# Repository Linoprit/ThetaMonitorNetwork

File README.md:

# ThetaMonitorNetwork

This project replaces TemperatureMonitor

What it does: Several slaves measure temperature, with DS18B20 and send their results to a master-station, via NRF24 modules. The master-station is connected to a Raspi, which hosts a database and a PHP-Server (LAMP-Config). With a browser, you can graphically see the temperature-profile of the last 24h. In the database every measurement is stored in 5 minute intervals. Also the slaves can drive a relay, to which a heating can be connected.

The old TemperatureMonitor run fine since some years now. Due to some instabilities with DS18B20 measurement, desired sensor extension, etc. I will develop this thing further in this project.

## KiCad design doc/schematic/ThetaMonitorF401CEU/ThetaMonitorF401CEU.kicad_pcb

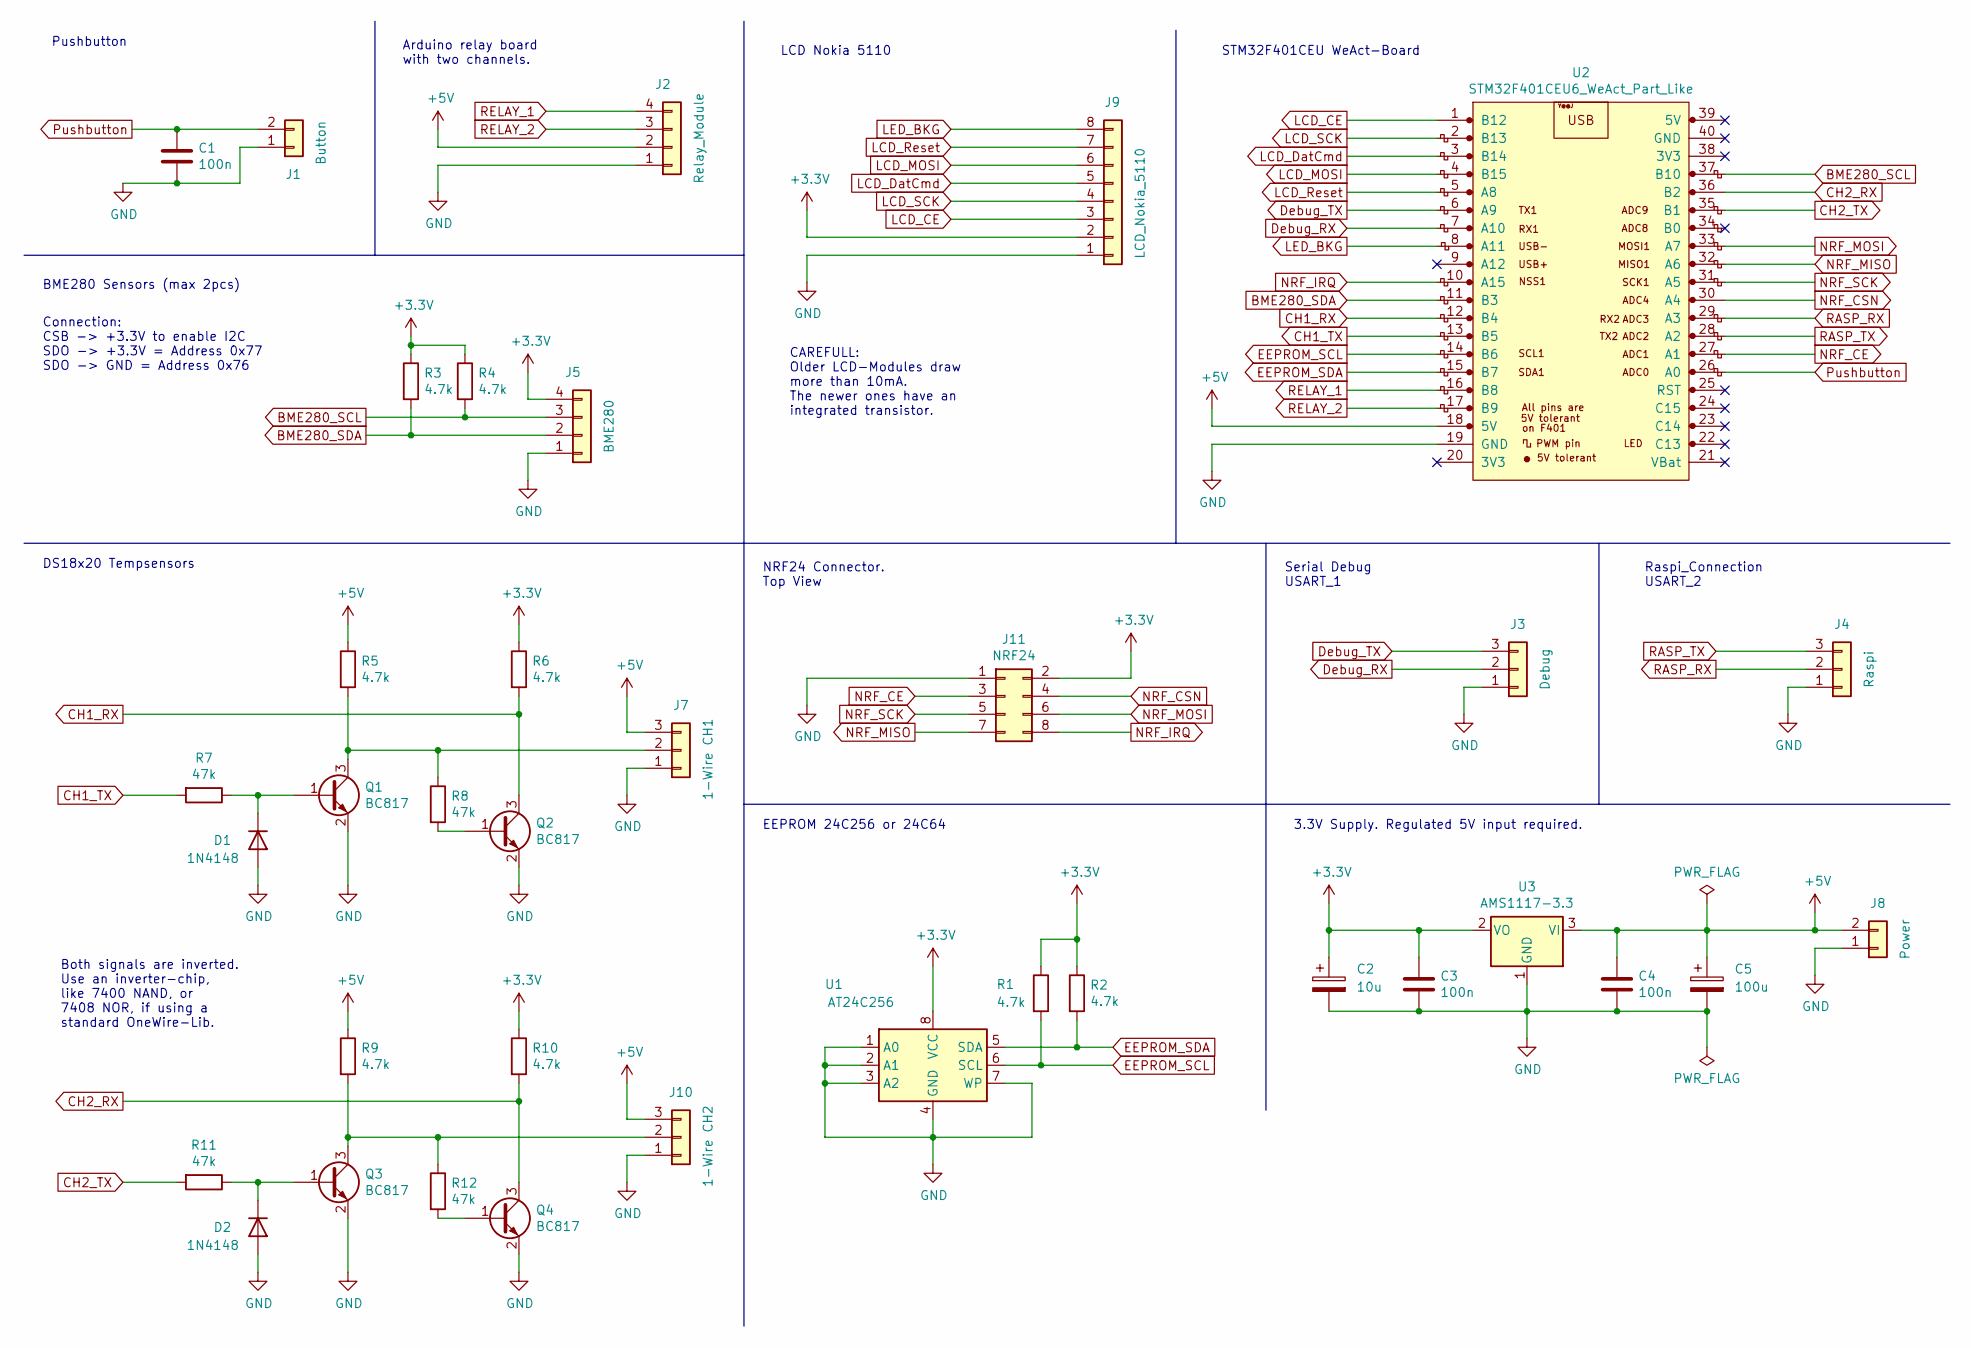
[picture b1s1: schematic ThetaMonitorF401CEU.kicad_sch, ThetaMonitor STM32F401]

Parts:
C1, C3, C4: 100n; C_1206_3216Metric_Pad1.33x1.80mm_HandSolder
C2: 10u; CP_Radial_D6.3mm_P2.50mm
C5: 100u; CP_Axial_L11.0mm_D8.0mm_P15.00mm_Horizontal
D1, D2: 1N4148; D_DO-35_SOD27_P7.62mm_Horizontal
J1: Button; Molex_KK-254_AE-6410-02A_1x02_P2.54mm_Vertical
J2: Relay_Module; Molex_KK-254_AE-6410-04A_1x04_P2.54mm_Vertical
J3: Debug; Molex_KK-254_AE-6410-03A_1x03_P2.54mm_Vertical
J4: Raspi; Molex_KK-254_AE-6410-03A_1x03_P2.54mm_Vertical
J5: BME280; Molex_KK-254_AE-6410-04A_1x04_P2.54mm_Vertical
J7: 1-Wire CH1; Molex_KK-254_AE-6410-03A_1x03_P2.54mm_Vertical
J8: Power; Molex_KK-254_AE-6410-02A_1x02_P2.54mm_Vertical
J9: LCD_Nokia_5110; Molex_KK-254_AE-6410-08A_1x08_P2.54mm_Vertical
J10: 1-Wire CH2; Molex_KK-254_AE-6410-03A_1x03_P2.54mm_Vertical
J11: NRF24; PinHeader_2x04_P2.54mm_Vertical
Q1, Q2, Q3, Q4: BC817; SOT-23
R1, R2, R3, R4, R5, R6, R9, R10: 4.7k; R_Axial_DIN0207_L6.3mm_D2.5mm_P7.62mm_Horizontal
R7, R8, R11, R12: 47k; R_Axial_DIN0207_L6.3mm_D2.5mm_P7.62mm_Horizontal
U1: AT24C256; DIP-8_W7.62mm
U2: STM32F401CEU6_WeAct_Part_Like; YAAJ_BluePill_1
U3: AMS1117-3.3; SOT-223-3_TabPin2

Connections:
+3V3: C2.1, C3.1, J5.4, J9.2, J11.2, R1.1, R2.1, R3.1, R4.1, R6.1, R10.1, U1.8 (VCC), U3.2 (VO)
+5V: C4.1, C5.1, J2.2, J7.3, J8.2, J10.3, R5.1, R9.1, U2.18 (5V), U3.3 (VI)
BME280_SCL: J5.3, R4.2, U2.37 (B10)
BME280_SDA: J5.2, R3.2, U2.11 (B3)
CH1_RX: Q2.3 (C), R6.2, U2.12 (B4)
CH1_TX: R7.2, U2.13 (B5)
CH2_RX: Q4.3 (C), R10.2, U2.36 (B2)
CH2_TX: R11.2, U2.35 (B1)
Debug_RX: J3.2, U2.7 (A10)
Debug_TX: J3.3, U2.6 (A9)
EEPROM_SCL: R1.2, U1.6 (SCL), U2.14 (B6)
EEPROM_SDA: R2.2, U1.5 (SDA), U2.15 (B7)
GND: C1.2, C2.2, C3.2, C4.2, C5.2, D1.2 (A), D2.2 (A), J1.1, J2.1, J3.1, J4.1, J5.1, J7.1, J8.1, J9.1, J10.1, J11.1, Q1.2 (E), Q2.2 (E), Q3.2 (E), Q4.2 (E), U1.1 (A0), U1.2 (A1), U1.3 (A2), U1.4 (GND), U1.7 (WP), U2.19 (GND), U3.1 (GND)
LCD_CE: J9.3, U2.1 (B12)
LCD_DatCmd: J9.5, U2.3 (B14)
LCD_MOSI: J9.6, U2.4 (B15)
LCD_Reset: J9.7, U2.5 (A8)
LCD_SCK: J9.4, U2.2 (B13)
LED_BKG: J9.8, U2.8 (A11)
NRF_CE: J11.3, U2.27 (A1)
NRF_CSN: J11.4, U2.30 (A4)
NRF_IRQ: J11.8, U2.10 (A15)
NRF_MISO: J11.7, U2.32 (A6)
NRF_MOSI: J11.6, U2.33 (A7)
NRF_SCK: J11.5, U2.31 (A5)
unnamed: D1.1 (K), Q1.1 (B), R7.1
unnamed: D2.1 (K), Q3.1 (B), R11.1
unnamed: J7.2, Q1.3 (C), R5.2, R8.1
unnamed: J10.2, Q3.3 (C), R9.2, R12.1
unnamed: Q2.1 (B), R8.2
unnamed: Q4.1 (B), R12.2
Pushbutton: C1.1, J1.2, U2.26 (A0)
RASP_RX: J4.2, U2.29 (A3)
RASP_TX: J4.3, U2.28 (A2)
RELAY_1: J2.4, U2.16 (B8)
RELAY_2: J2.3, U2.17 (B9)

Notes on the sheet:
LCD Nokia 5110
Raspi_Connection USART_2
BME280 Sensors (max 2pcs)
3.3V Supply. Regulated 5V input required.
EEPROM 24C256 or 24C64
Both signals are inverted. Use an inverter-chip, like 7400 NAND, or 7408 NOR, if using a standard OneWire-Lib.
Arduino relay board with two channels.
Pushbutton
STM32F401CEU WeAct-Board
NRF24 Connector. Top View
CAREFULL: Older LCD-Modules draw more than 10mA. The newer ones have an integrated transistor.
DS18x20 Tempsensors
Serial Debug USART_1
Connection: CSB -> +3.3V to enable I2C SDO -> +3.3V = Address 0x77 SDO -> GND = Address 0x76

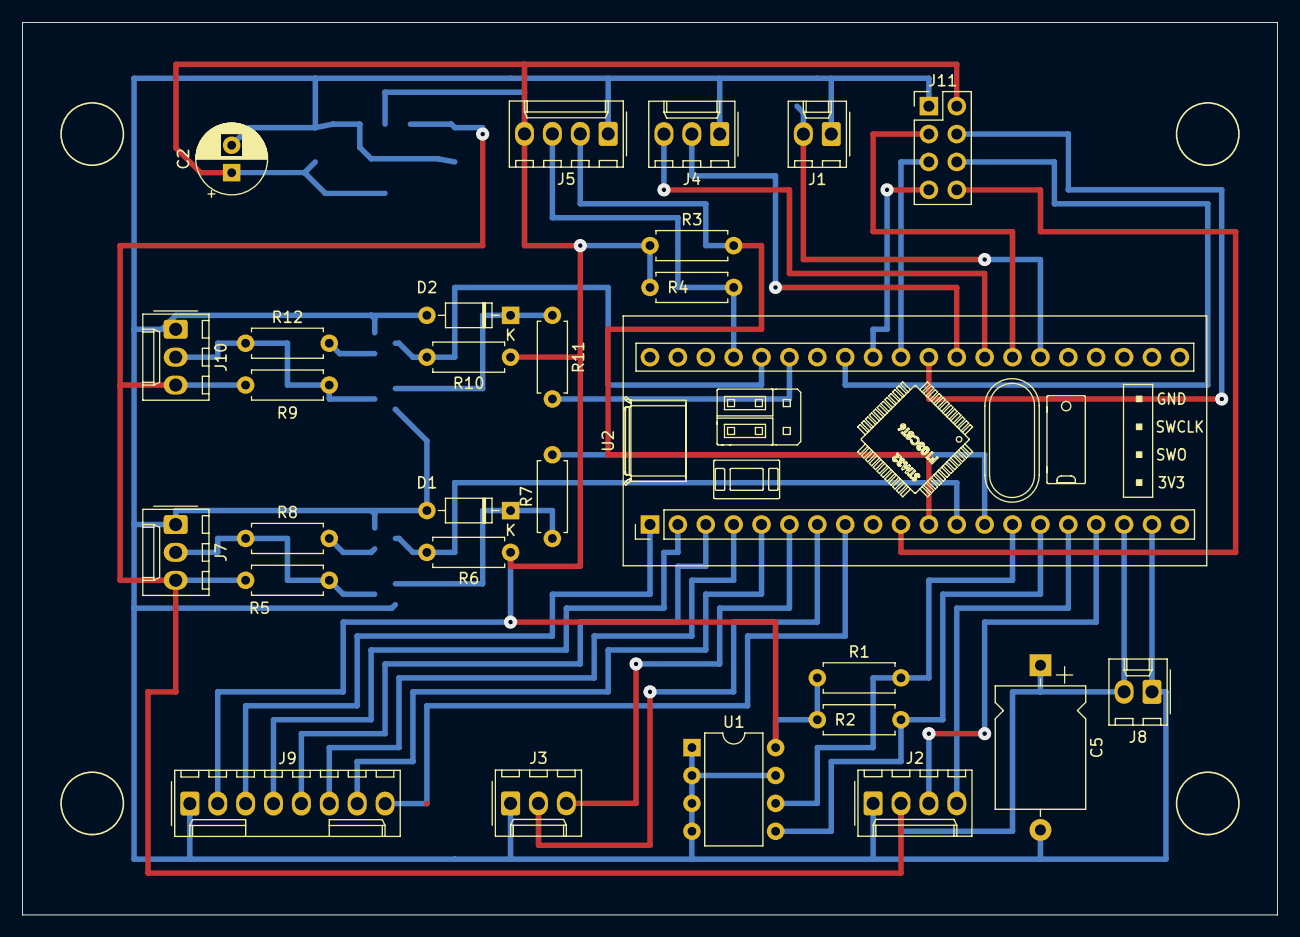
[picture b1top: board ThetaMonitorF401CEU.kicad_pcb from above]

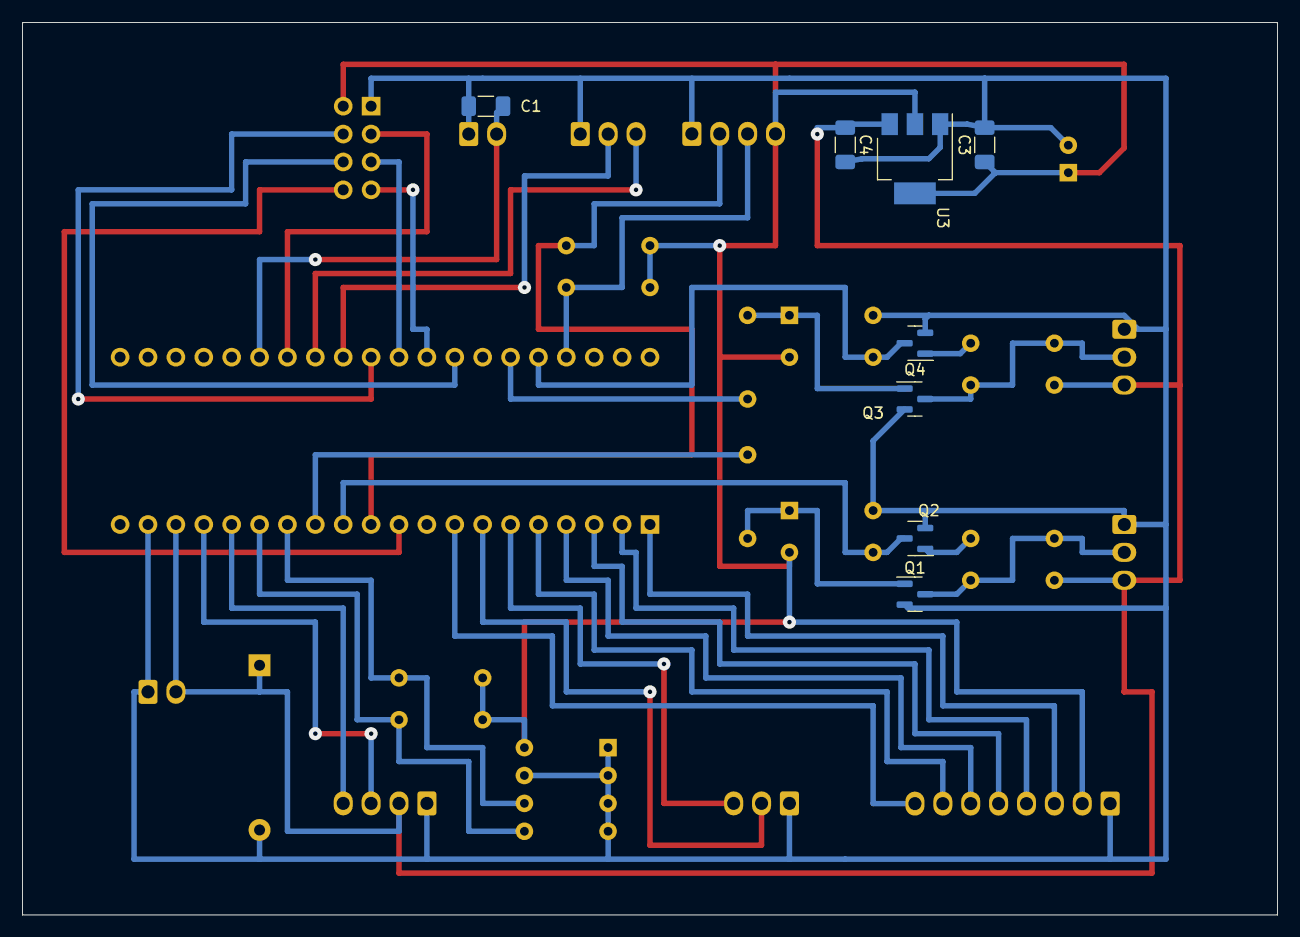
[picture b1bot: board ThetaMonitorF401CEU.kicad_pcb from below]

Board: 2 copper layers, 114.3 x 81.3 mm, 36 parts (8 on the bottom side), 36 nets.

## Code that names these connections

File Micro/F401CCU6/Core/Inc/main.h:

/* USER CODE BEGIN Header */
/**
  ******************************************************************************
  * @file           : main.h
  * @brief          : Header for main.c file.
  *                   This file contains the common defines of the application.
  ******************************************************************************
  * @attention
  *
  * Copyright (c) 2022 STMicroelectronics.
  * All rights reserved.
  *
  * This software is licensed under terms that can be found in the LICENSE file
  * in the root directory of this software component.
  * If no LICENSE file comes with this software, it is provided AS-IS.
  *
  ******************************************************************************
  */
/* USER CODE END Header */

/* Define to prevent recursive inclusion -------------------------------------*/
#ifndef __MAIN_H
#define __MAIN_H

#ifdef __cplusplus
extern "C" {
#endif

/* Includes ------------------------------------------------------------------*/
#include "stm32f4xx_hal.h"

/* Private includes ----------------------------------------------------------*/
/* USER CODE BEGIN Includes */

/* USER CODE END Includes */

/* Exported types ------------------------------------------------------------*/
/* USER CODE BEGIN ET */

/* USER CODE END ET */

/* Exported constants --------------------------------------------------------*/
/* USER CODE BEGIN EC */

/* USER CODE END EC */

/* Exported macro ------------------------------------------------------------*/
/* USER CODE BEGIN EM */

/* USER CODE END EM */

/* Exported functions prototypes ---------------------------------------------*/
void Error_Handler(void);

/* USER CODE BEGIN EFP */

/* USER CODE END EFP */

/* Private defines -----------------------------------------------------------*/
#define LED_Pin GPIO_PIN_13
#define LED_GPIO_Port GPIOC
#define BUTTON_1_Pin GPIO_PIN_0
#define BUTTON_1_GPIO_Port GPIOA
#define BUTTON_1_EXTI_IRQn EXTI0_IRQn
#define NRF_CE_Pin GPIO_PIN_1
#define NRF_CE_GPIO_Port GPIOA
#define NRF_CSN_Pin GPIO_PIN_4
#define NRF_CSN_GPIO_Port GPIOA
#define NRF_SCK_Pin GPIO_PIN_5
#define NRF_SCK_GPIO_Port GPIOA
#define NRF_MISO_Pin GPIO_PIN_6
#define NRF_MISO_GPIO_Port GPIOA
#define NRF_MOSI_Pin GPIO_PIN_7
#define NRF_MOSI_GPIO_Port GPIOA
#define DebLed_1_Pin GPIO_PIN_0
#define DebLed_1_GPIO_Port GPIOB
#define CH2_TX_Pin GPIO_PIN_1
#define CH2_TX_GPIO_Port GPIOB
#define CH2_RX_Pin GPIO_PIN_2
#define CH2_RX_GPIO_Port GPIOB
#define BME280_SCL_Pin GPIO_PIN_10
#define BME280_SCL_GPIO_Port GPIOB
#define LCD_CE_Pin GPIO_PIN_12
#define LCD_CE_GPIO_Port GPIOB
#define LCD_SCK_Pin GPIO_PIN_13
#define LCD_SCK_GPIO_Port GPIOB
#define LCD_DC_Pin GPIO_PIN_14
#define LCD_DC_GPIO_Port GPIOB
#define LCD_MOSI_Pin GPIO_PIN_15
#define LCD_MOSI_GPIO_Port GPIOB
#define LCD_Reset_Pin GPIO_PIN_8
#define LCD_Reset_GPIO_Port GPIOA
#define LCD_BCKLT_Pin GPIO_PIN_11
#define LCD_BCKLT_GPIO_Port GPIOA
#define DebLed_2_Pin GPIO_PIN_12
#define DebLed_2_GPIO_Port GPIOA
#define NRF_IRQ_Pin GPIO_PIN_15
#define NRF_IRQ_GPIO_Port GPIOA
#define NRF_IRQ_EXTI_IRQn EXTI15_10_IRQn
#define BME280_SDA_Pin GPIO_PIN_3
#define BME280_SDA_GPIO_Port GPIOB
#define CH1_RX_Pin GPIO_PIN_4
#define CH1_RX_GPIO_Port GPIOB
#define CH1_TX_Pin GPIO_PIN_5
#define CH1_TX_GPIO_Port GPIOB
#define EEPROM_SCL_Pin GPIO_PIN_6
#define EEPROM_SCL_GPIO_Port GPIOB
#define EEPROM_SDA_Pin GPIO_PIN_7
#define EEPROM_SDA_GPIO_Port GPIOB
#define RELAY_1__Pin GPIO_PIN_8
#define RELAY_1__GPIO_Port GPIOB
#define RELAY_2__Pin GPIO_PIN_9
#define RELAY_2__GPIO_Port GPIOB
/* USER CODE BEGIN Private defines */

/* USER CODE END Private defines */

#ifdef __cplusplus
}
#endif

#endif /* __MAIN_H */

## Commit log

2021-02-14 New schematic.
2021-06-05 All ThetaMonitor parts put together.
2021-11-01 Framework-directory centralized
2021-11-05 HG: OneWire is working now.
2021-11-07 BME280 and DS18B20 is working now. Still simple console output only.
2021-12-13 Measurement task almost finished.
2021-12-23 LCD working, nRF basis-functions working.
2022-01-05 Switched to STM32F401CCU6
2022-01-05 stash-dir deleted
2022-02-20 Architecture documented.
2022-06-13 Beginning with nRF Gateway to serial raspi
2022-06-13 Moved some directories
2022-12-13 Python module started
2022-12-15 Going on with NRF24 data-put-through.
2022-12-26 Remote connection works the first time, even with dynamic payload
2022-12-26 check-relays implemented, sensor-timeout added and some ToDos done.
2022-12-26 nothing committed?
2023-01-05 First working Version
    Button actions still missing, Relay-function is untested
2023-01-06 TableID parser done
2023-01-08 ThetaMonitor programming E2 tool finished, but not tested
2023-01-15 Python based TableID programmer is working. Next step: the deamon
2023-02-12 Further on to shovel data into the db.
2023-02-12 once again...
2023-04-02 Database update working
2023-04-25 Work in Progress. Creating html module.
2023-07-15 HG: GUI, serial-port selector fixed
2023-08-06 catch NAN problem when writing to DB
2023-08-06 LastUpdateTick inserted into SensorDataTable. Logfile rolling added.
2023-08-13 Working on HTML-output
2023-08-21 Further on with HTML-creation
2023-08-25 Html-creator: Work in progress
2023-08-27 Html-creator and plot-creator finished
2023-08-27 old qt version deleted
2023-08-27 x86 cleaned
2023-08-27 old php sources deleted
2023-08-29 Relay issue fixed. Table_id updated.
2023-09-30 Erste Inbetriebnahme
2023-09-30 Daemon separated from THS
2023-10-06 Fixed x-axis plot issue
2023-10-17 PlotCreator Y-Axis, denser labeling
2023-11-11 nRF channel changed, some start up delay increased
2023-11-12 PlotCreator changed axis-settings
2023-11-26 Renamed Micro -> Probes
2023-11-26 new directory
2023-11-26 Framework moved into Modules
2023-11-26 sync
2023-11-26 Beginning with RF24 Repeater
